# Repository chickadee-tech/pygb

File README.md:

# pygb
A Python powered GameBoy-compatible cartridge with a SAMD51

The PCB must be 0.8mm thick to fit in an existing game cart. Prototypes are done with OSH Park's 2 oz 0.8mm stackup.

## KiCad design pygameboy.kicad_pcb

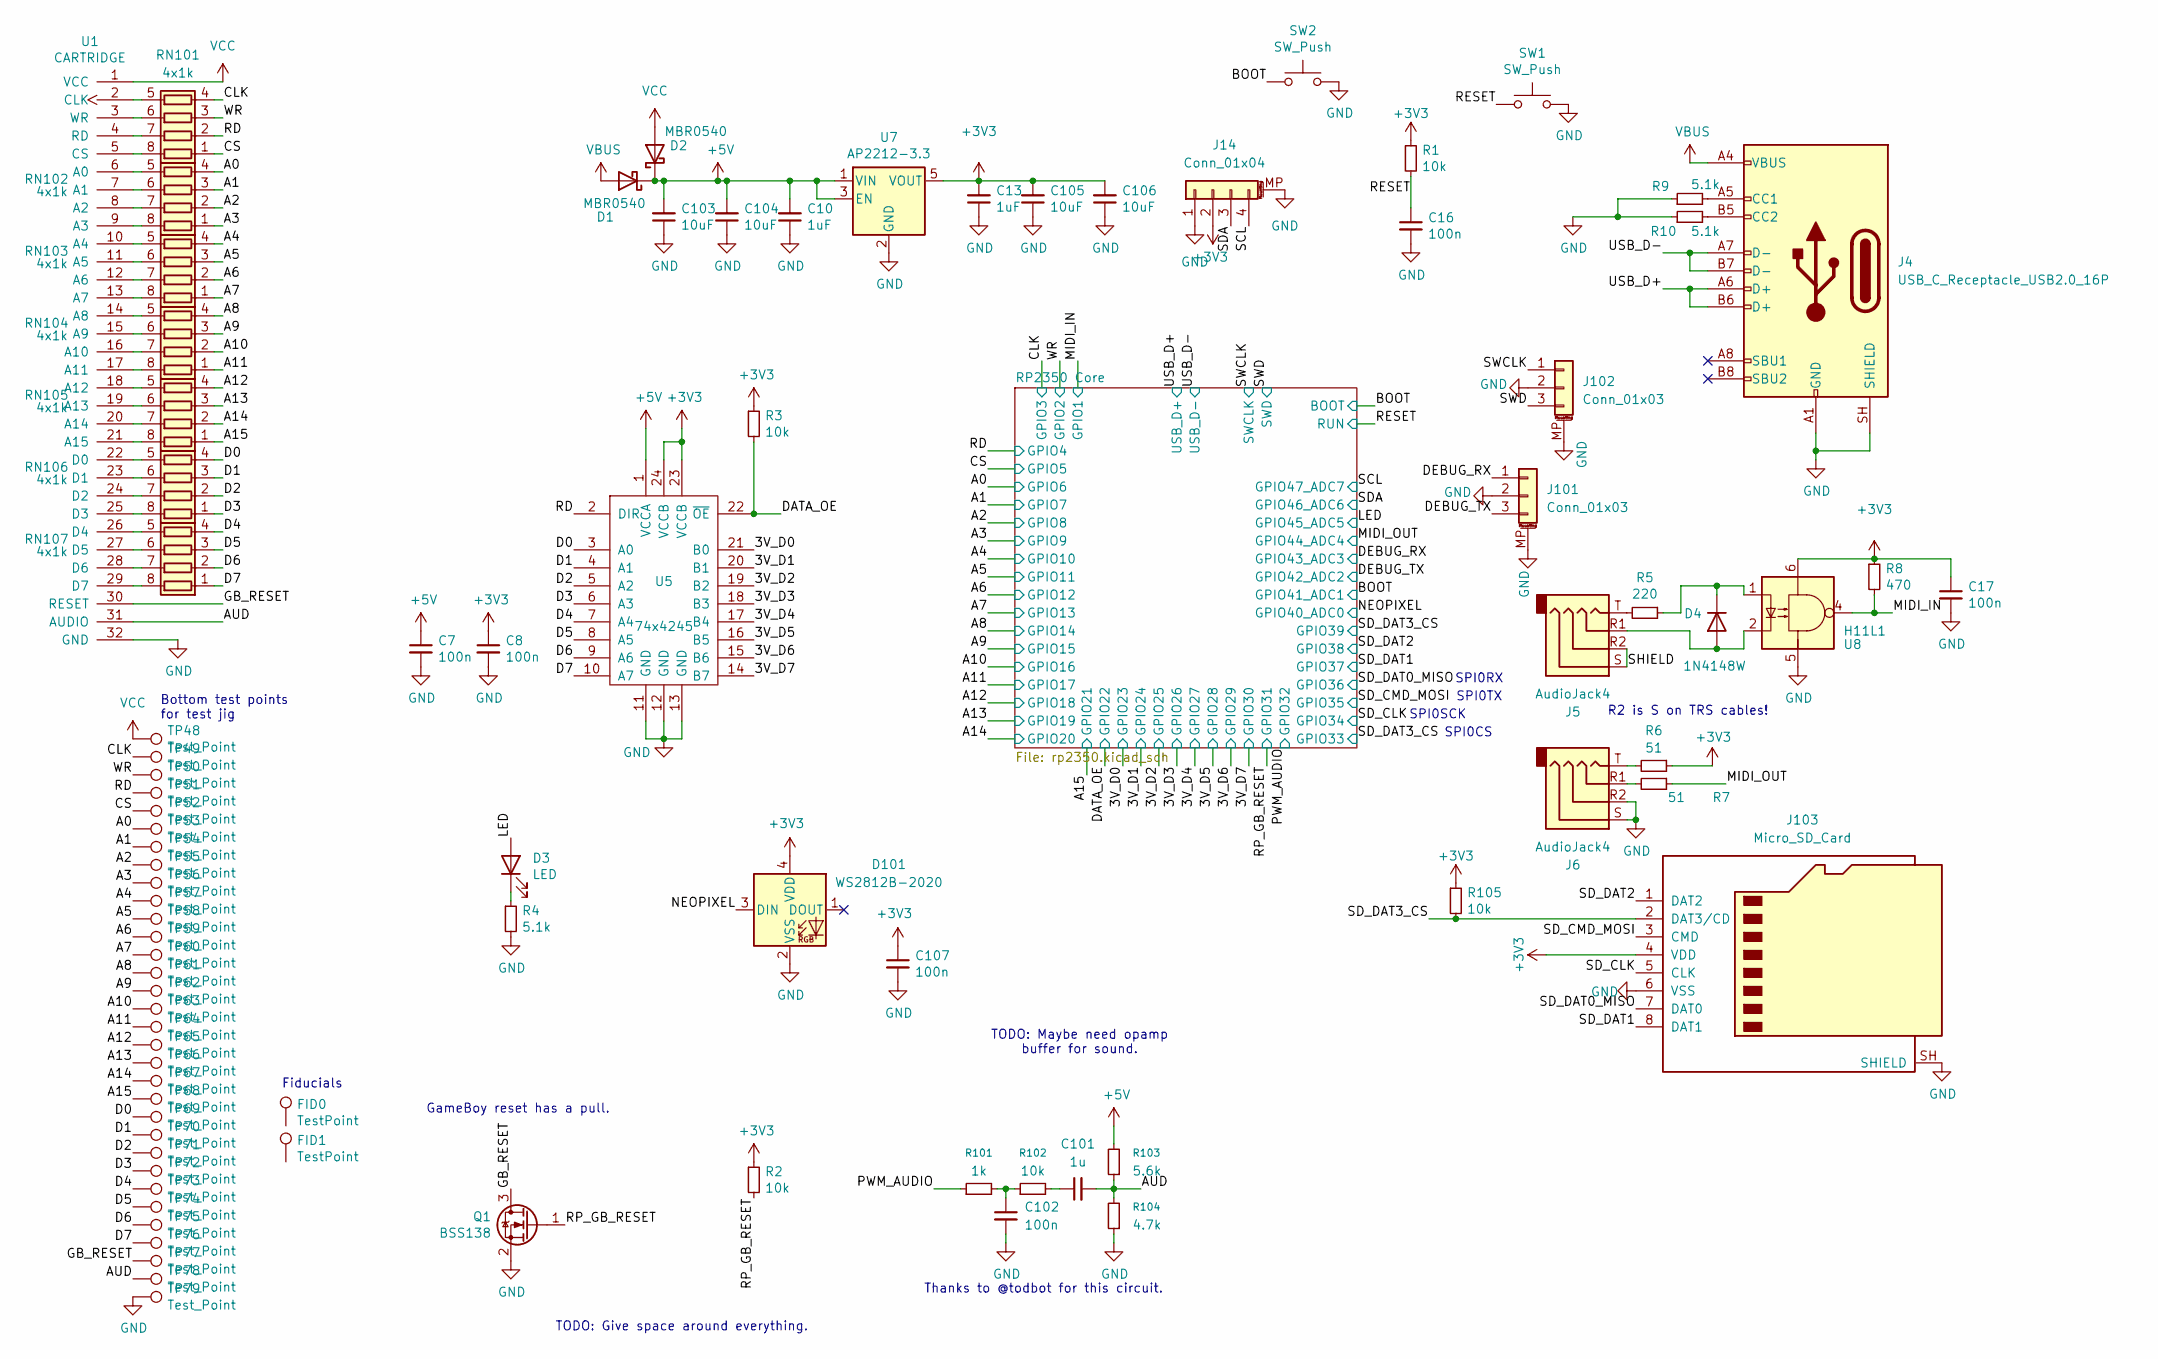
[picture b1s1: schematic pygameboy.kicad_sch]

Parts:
C7, C8, C16, C17, C107: 100n; C_0402_1005Metric
C10, C13: 1uF; C_0603_1608Metric
C101: 1u; C_0603_1608Metric_Pad1.08x0.95mm_HandSolder
C102: 100n; C_0603_1608Metric_Pad1.08x0.95mm_HandSolder
C103, C104, C105, C106: 10uF; C_0805_2012Metric
D1, D2: MBR0540; D_SOD-123
D3: LED; LED_0603_1608Metric
D4: 1N4148W; D_SOD-523
D101: WS2812B-2020; LED_WS2812B-2020_PLCC4_2.0x2.0mm
FID0, FID1: TestPoint; Fiducial_1mm_Mask2mm
J4: USB_C_Receptacle_USB2.0_16P; USB_C_Receptacle_HRO_TYPE-C-31-M-31
J5, J6: AudioJack4; Jack_3.5mm_PJ320D_Horizontal
J14: Conn_01x04; JST_SH_BM04B-SRSS-TB_1x04-1MP_P1.00mm_Vertical
J101, J102: Conn_01x03; JST_SH_BM03B-SRSS-TB_1x03-1MP_P1.00mm_Vertical
J103: Micro_SD_Card; TF-027-HXXX
Q1: BSS138; SOT-23
R1, R2, R3, R105: 10k; R_0402_1005Metric
R4, R9, R10: 5.1k; R_0402_1005Metric
R5: 220; R_0402_1005Metric
R6, R7: 51; R_0402_1005Metric
R8: 470; R_0402_1005Metric
R101: 1k; R_0603_1608Metric_Pad0.98x0.95mm_HandSolder
R102: 10k; R_0603_1608Metric_Pad0.98x0.95mm_HandSolder
R103: 5.6k; R_0603_1608Metric_Pad0.98x0.95mm_HandSolder
R104: 4.7k; R_0603_1608Metric_Pad0.98x0.95mm_HandSolder
RN101, RN102, RN103, RN104, RN105, RN106, RN107: 4x1k; R_Array_Convex_4x0603
SW1, SW2: SW_Push; TS-1185
TP48, TP49, TP50, TP51, TP52, TP53, TP54, TP55, TP56, TP57, TP58, TP59, TP60, TP61, TP62, TP63, TP64, TP65, TP66, TP67, TP68, TP69, TP70, TP71, TP72, TP73, TP74, TP75, TP76, TP77, TP78, TP79: Test_Point; TestPoint_Pad_D1.5mm
U1: CARTRIDGE; Cartridge
U5: 74x4245; TSSOP-24_4.4x7.8mm_P0.65mm
U7: AP2212-3.3; SOT-23-5
U8: H11L1; SMDIP-6_W9.53mm

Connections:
+3V3: C8.1, C13.2, C17.1, C105.2, C106.2, C107.1, D101.4 (VDD), J14.2, J103.4 (VDD), R1.1, R2.1, R3.1, R6.1, R8.1, R105.1, U5.23 (VCCB), U5.24 (VCCB), U7.5 (VOUT), U8.6; also elsewhere on the board
+5V: C7.1, C10.2, C103.2, C104.2, D1.1 (K), D2.1 (K), R103.2, U5.1 (VCCA), U7.1 (VIN), U7.3 (EN)
/3V_D0: U5.21 (B0); also elsewhere on the board
/3V_D1: U5.20 (B1); also elsewhere on the board
/3V_D2: U5.19 (B2); also elsewhere on the board
/3V_D3: U5.18 (B3); also elsewhere on the board
/3V_D4: U5.17 (B4); also elsewhere on the board
/3V_D5: U5.16 (B5); also elsewhere on the board
/3V_D6: U5.15 (B6); also elsewhere on the board
/3V_D7: U5.14 (B7); also elsewhere on the board
/A0: RN102.4 (R4.1), TP53.1 (1_1); also elsewhere on the board
/A1: RN102.3 (R3.1), TP54.1 (1_1); also elsewhere on the board
/A2: RN102.2 (R2.1), TP55.1 (1_1); also elsewhere on the board
/A3: RN102.1 (R1.1), TP56.1 (1_1); also elsewhere on the board
/A4: RN103.4 (R4.1), TP57.1 (1_1); also elsewhere on the board
/A5: RN103.3 (R3.1), TP58.1 (1_1); also elsewhere on the board
/A6: RN103.2 (R2.1), TP59.1 (1_1); also elsewhere on the board
/A7: RN103.1 (R1.1), TP60.1 (1_1); also elsewhere on the board
/A8: RN104.4 (R4.1), TP61.1 (1_1); also elsewhere on the board
/A9: RN104.3 (R3.1), TP62.1 (1_1); also elsewhere on the board
/A10: RN104.2 (R2.1), TP63.1 (1_1); also elsewhere on the board
/A11: RN104.1 (R1.1), TP64.1 (1_1); also elsewhere on the board
/A12: RN105.4 (R4.1), TP65.1 (1_1); also elsewhere on the board
/A13: RN105.3 (R3.1), TP66.1 (1_1); also elsewhere on the board
/A14: RN105.2 (R2.1), TP67.1 (1_1); also elsewhere on the board
/A15: RN105.1 (R1.1), TP68.1 (1_1); also elsewhere on the board
/AUD: C101.2, R103.1, R104.2, TP78.1 (1_1), U1.31 (AUDIO)
/BOOT: SW2.1; also elsewhere on the board
/CLK: RN101.4 (R4.1), TP49.1 (1_1); also elsewhere on the board
/CS: RN101.1 (R1.1), TP52.1 (1_1); also elsewhere on the board
/D0: RN106.4 (R4.1), TP69.1 (1_1), U5.3 (A0)
/D1: RN106.3 (R3.1), TP70.1 (1_1), U5.4 (A1)
/D2: RN106.2 (R2.1), TP71.1 (1_1), U5.5 (A2)
/D3: RN106.1 (R1.1), TP72.1 (1_1), U5.6 (A3)
/D4: RN107.4 (R4.1), TP73.1 (1_1), U5.7 (A4)
/D5: RN107.3 (R3.1), TP74.1 (1_1), U5.8 (A5)
/D6: RN107.2 (R2.1), TP75.1 (1_1), U5.9 (A6)
/D7: RN107.1 (R1.1), TP76.1 (1_1), U5.10 (A7)
/DATA_OE: R3.2, U5.22 (~OE); also elsewhere on the board
/DEBUG_RX: J101.1; also elsewhere on the board
/DEBUG_TX: J101.3; also elsewhere on the board
/GB_RESET: Q1.3 (D), TP77.1 (1_1), U1.30 (RESET)
/LED: D3.2 (A); also elsewhere on the board
/MIDI_IN: R8.2, U8.4; also elsewhere on the board
/MIDI_OUT: R7.1; also elsewhere on the board
/NEOPIXEL: D101.3 (DIN); also elsewhere on the board
/PWM_AUDIO: R101.1; also elsewhere on the board
/RD: RN101.2 (R2.1), TP51.1 (1_1), U5.2 (DIR); also elsewhere on the board
/RESET: C16.1, R1.2, SW1.1; also elsewhere on the board
/RP_GB_RESET: Q1.1 (G), R2.2; also elsewhere on the board
/SCL: J14.4; also elsewhere on the board
/SDA: J14.3; also elsewhere on the board
/SD_CLK: J103.5 (CLK); also elsewhere on the board
/SD_CMD_MOSI: J103.3 (CMD); also elsewhere on the board
/SD_DAT0_MISO: J103.7 (DAT0); also elsewhere on the board
/SD_DAT1: J103.8 (DAT1); also elsewhere on the board
/SD_DAT2: J103.1 (DAT2); also elsewhere on the board
/SD_DAT3_CS: J103.2 (DAT3/CD), R105.2; also elsewhere on the board
/SHIELD: J5.R2, J5.S
/SWCLK: J102.1; also elsewhere on the board
/SWD: J102.3; also elsewhere on the board
/USB_D+: J4.A6 (D+), J4.B6 (D+); also elsewhere on the board
/USB_D-: J4.A7 (D-), J4.B7 (D-); also elsewhere on the board
/WR: RN101.3 (R3.1), TP50.1 (1_1); also elsewhere on the board
GND: C7.2, C8.2, C10.1, C13.1, C16.2, C17.2, C102.2, C103.1, C104.1, C105.1, C106.1, C107.2, D101.2 (VSS), J4.A1 (GND), J4.A12 (GND), J4.B1 (GND), J4.B12 (GND), J4.SH (SHIELD), J6.R2, J6.S, J14.1, J14.MP (MountPin), J101.2, J101.MP (MountPin), J102.2, J102.MP (MountPin), J103.6 (VSS), J103.SH (SHIELD), Q1.2 (S), R4.2, R9.1, R10.1, R104.1, SW1.2, SW2.2, TP79.1 (1_1), U1.32 (GND), U5.11 (GND), U5.12 (GND), U5.13 (GND), U7.2 (GND), U8.5; also elsewhere on the board
unnamed: C101.1, R102.2
unnamed: C102.1, R101.2, R102.1
unnamed: D3.1 (K), R4.1
unnamed: D4.2 (A), J5.R1, U8.2
unnamed: D4.1 (K), R5.1, U8.1
unnamed: J4.A5 (CC1), R9.2
unnamed: J4.B5 (CC2), R10.2
unnamed: J5.T, R5.2
unnamed: J6.R1, R7.2
unnamed: J6.T, R6.2
unnamed: RN101.8 (R1.2), U1.5 (CS)
unnamed: RN101.7 (R2.2), U1.4 (RD)
unnamed: RN101.6 (R3.2), U1.3 (WR)
unnamed: RN101.5 (R4.2), U1.2 (CLK)
unnamed: RN102.8 (R1.2), U1.9 (A3)
unnamed: RN102.7 (R2.2), U1.8 (A2)
unnamed: RN102.6 (R3.2), U1.7 (A1)
unnamed: RN102.5 (R4.2), U1.6 (A0)
unnamed: RN103.8 (R1.2), U1.13 (A7)
unnamed: RN103.7 (R2.2), U1.12 (A6)
unnamed: RN103.6 (R3.2), U1.11 (A5)
unnamed: RN103.5 (R4.2), U1.10 (A4)
unnamed: RN104.8 (R1.2), U1.17 (A11)
unnamed: RN104.7 (R2.2), U1.16 (A10)
unnamed: RN104.6 (R3.2), U1.15 (A9)
unnamed: RN104.5 (R4.2), U1.14 (A8)
unnamed: RN105.8 (R1.2), U1.21 (A15)
unnamed: RN105.7 (R2.2), U1.20 (A14)
unnamed: RN105.6 (R3.2), U1.19 (A13)
unnamed: RN105.5 (R4.2), U1.18 (A12)
unnamed: RN106.8 (R1.2), U1.25 (D3)
unnamed: RN106.7 (R2.2), U1.24 (D2)
unnamed: RN106.6 (R3.2), U1.23 (D1)
unnamed: RN106.5 (R4.2), U1.22 (D0)
unnamed: RN107.8 (R1.2), U1.29 (D7)
unnamed: RN107.7 (R2.2), U1.28 (D6)
unnamed: RN107.6 (R3.2), U1.27 (D5)
unnamed: RN107.5 (R4.2), U1.26 (D4)
VBUS: D1.2 (A), J4.A4 (VBUS), J4.A9 (VBUS), J4.B4 (VBUS), J4.B9 (VBUS)
VCC: D2.2 (A), TP48.1 (1_1), U1.1 (VCC)

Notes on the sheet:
SPI0TX
R2 is S on TRS cables!
TODO: Maybe need opamp buffer for sound.
SPI0RX
SPI0CS
Thanks to @todbot for this circuit.
GameBoy reset has a pull.
SPI0SCK
TODO: Give space around everything.
Fiducials
Bottom test points for test jig

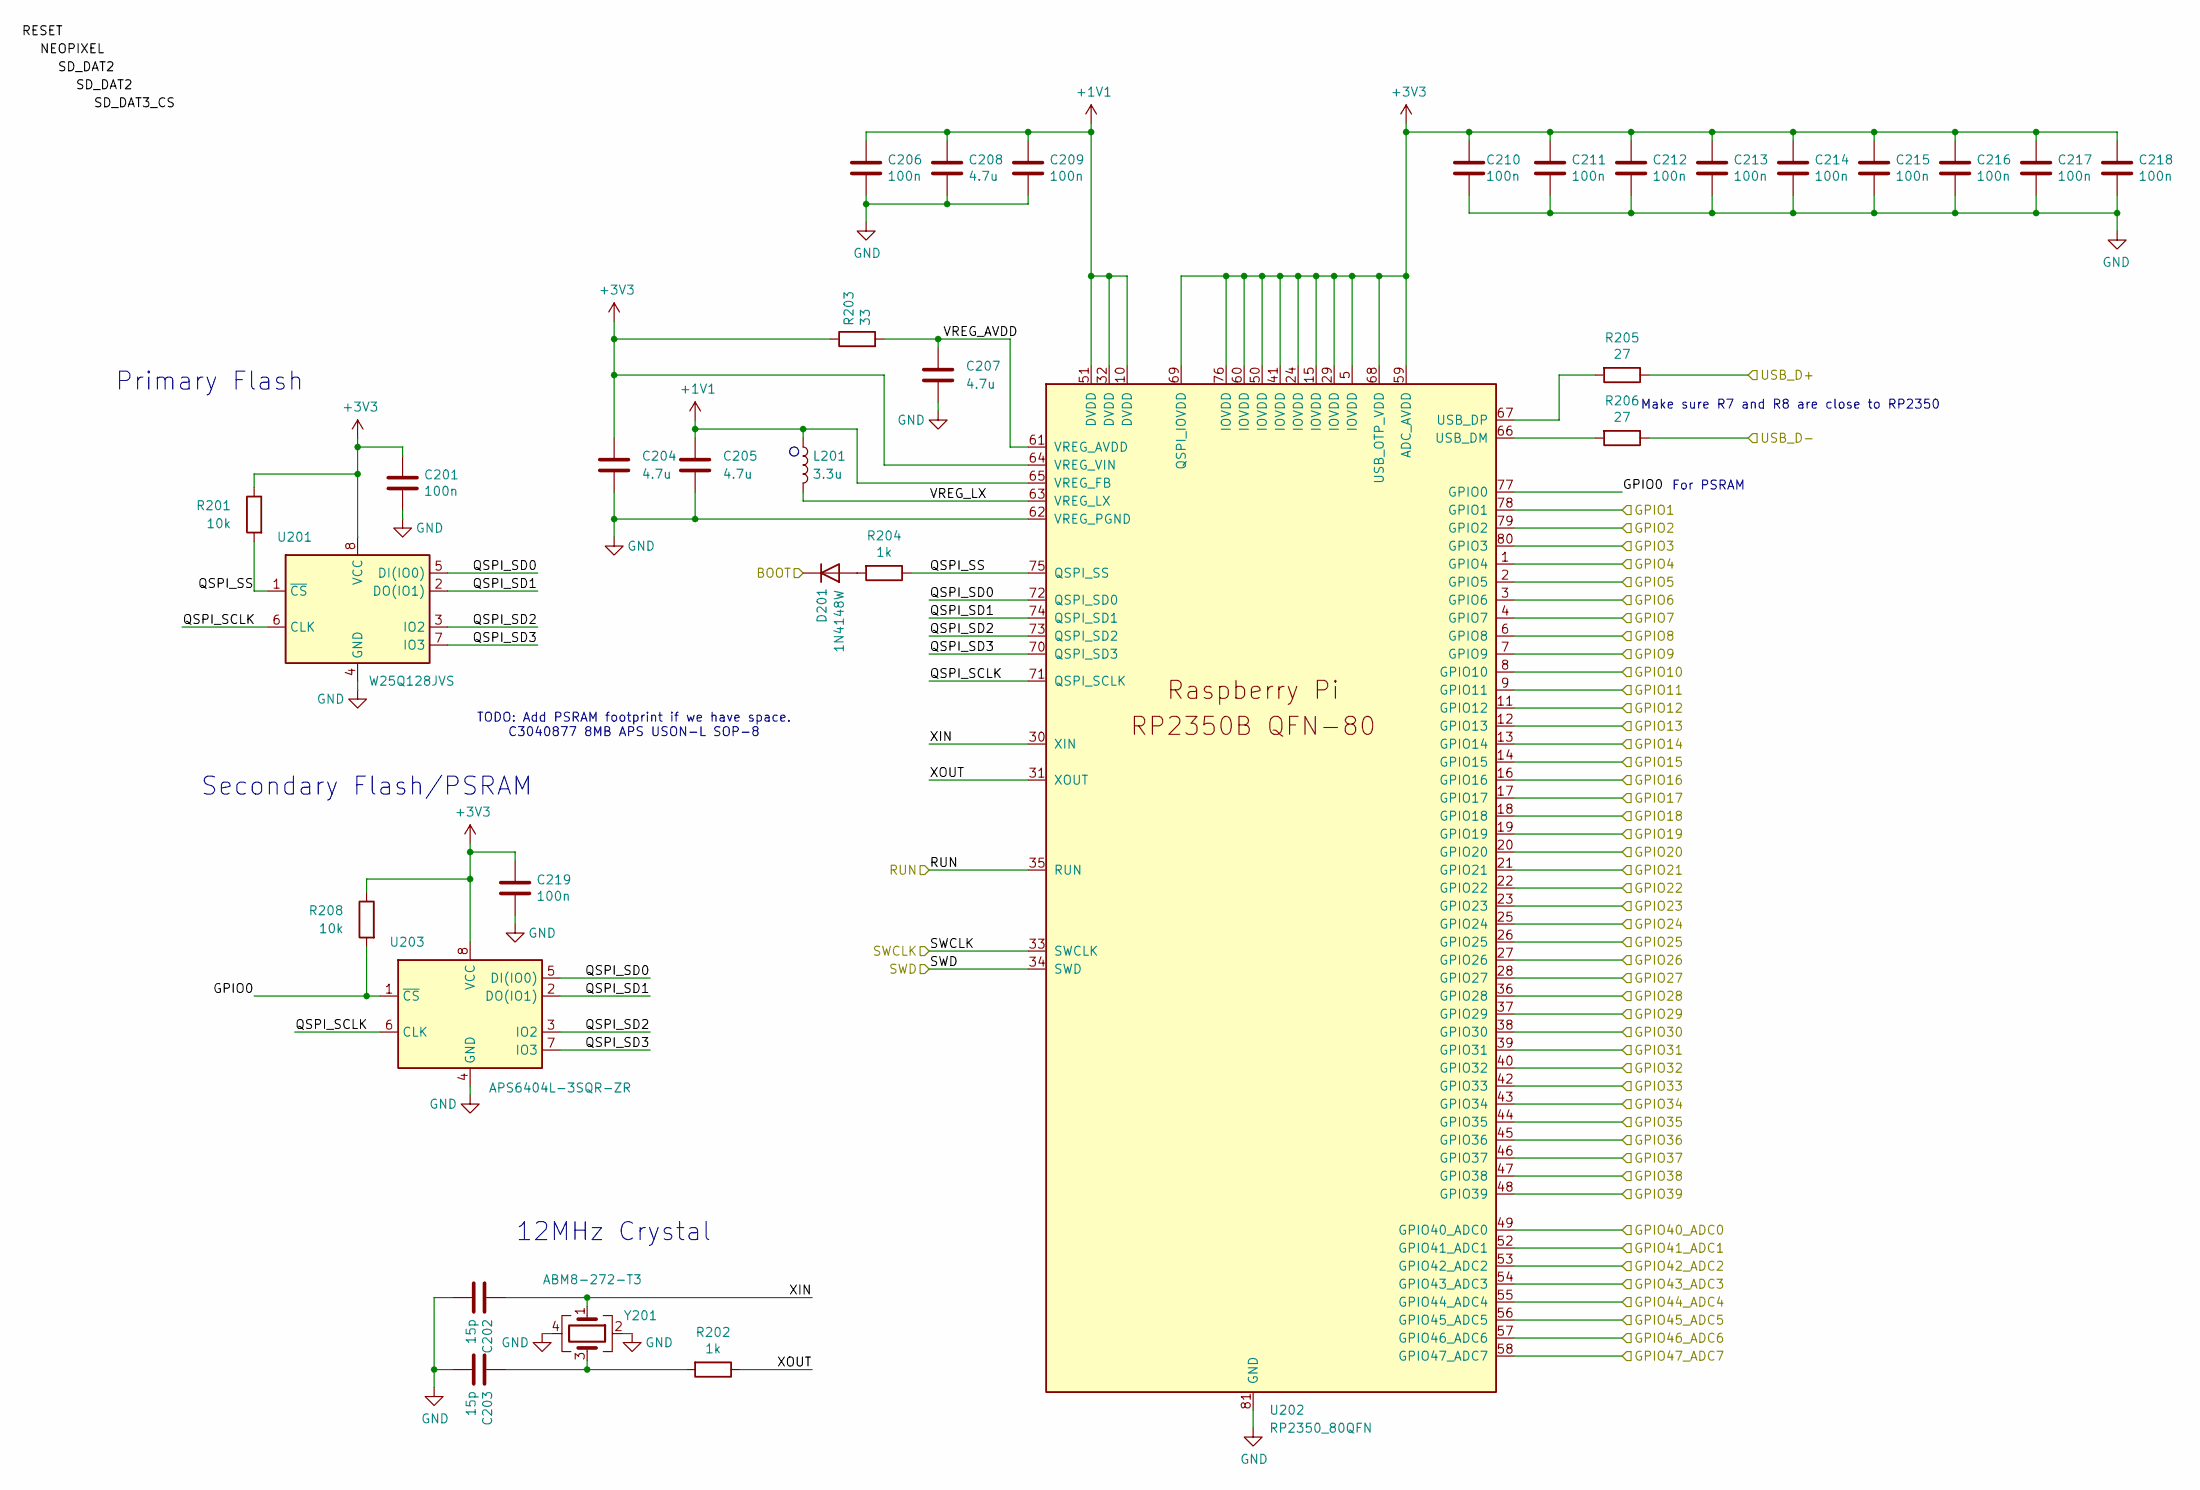
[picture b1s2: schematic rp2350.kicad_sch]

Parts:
C201, C206, C209, C210, C211, C212, C213, C214, C215, C216, C217, C218, C219: 100n; C_0402_1005Metric
C202, C203: 15p; C_0402_1005Metric
C204, C205: 4.7u; C_0402_1005Metric_small_pads
C207, C208: 4.7u; C_0805_2012Metric
D201: 1N4148W; D_SOD-523
L201: 3.3u; L_pol_2016
R201, R208: 10k; R_0402_1005Metric
R202, R204: 1k; R_0402_1005Metric
R203: 33; R_0402_1005Metric
R205, R206: 27; R_0402_1005Metric
U201: W25Q128JVS; SOIC-8_5.3x5.3mm_P1.27mm
U202: RP2350_80QFN; QFN-80-1EP_10x10mm_P0.4mm_EP3.4x3.4mm_ThermalVias
U203: APS6404L-3SQR-ZR; SOP-8_3.76x4.96mm_P1.27mm
Y201: ABM8-272-T3; Crystal_SMD_3225-4Pin_3.2x2.5mm

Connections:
+1V1: C205.1, C206.1, C208.1, C209.1, L201.1, U202.10 (DVDD), U202.32 (DVDD), U202.51 (DVDD), U202.65 (VREG_FB)
+3V3: C201.1, C204.1, C210.1, C211.1, C212.1, C213.1, C214.1, C215.1, C216.1, C217.1, C218.1, C219.1, R201.1, R203.1, R208.1, U201.8 (VCC), U202.5 (IOVDD), U202.15 (IOVDD), U202.24 (IOVDD), U202.29 (IOVDD), U202.41 (IOVDD), U202.50 (IOVDD), U202.59 (ADC_AVDD), U202.60 (IOVDD), U202.64 (VREG_VIN), U202.68 (USB_OTP_VDD), U202.69 (QSPI_IOVDD), U202.76 (IOVDD), U203.8 (VCC); also elsewhere on the board
/3V_D0: U202.23 (GPIO23); also elsewhere on the board
/3V_D1: U202.25 (GPIO24); also elsewhere on the board
/3V_D2: U202.26 (GPIO25); also elsewhere on the board
/3V_D3: U202.27 (GPIO26); also elsewhere on the board
/3V_D4: U202.28 (GPIO27); also elsewhere on the board
/3V_D5: U202.36 (GPIO28); also elsewhere on the board
/3V_D6: U202.37 (GPIO29); also elsewhere on the board
/3V_D7: U202.38 (GPIO30); also elsewhere on the board
/A0: U202.3 (GPIO6); also elsewhere on the board
/A1: U202.4 (GPIO7); also elsewhere on the board
/A2: U202.6 (GPIO8); also elsewhere on the board
/A3: U202.7 (GPIO9); also elsewhere on the board
/A4: U202.8 (GPIO10); also elsewhere on the board
/A5: U202.9 (GPIO11); also elsewhere on the board
/A6: U202.11 (GPIO12); also elsewhere on the board
/A7: U202.12 (GPIO13); also elsewhere on the board
/A8: U202.13 (GPIO14); also elsewhere on the board
/A9: U202.14 (GPIO15); also elsewhere on the board
/A10: U202.16 (GPIO16); also elsewhere on the board
/A11: U202.17 (GPIO17); also elsewhere on the board
/A12: U202.18 (GPIO18); also elsewhere on the board
/A13: U202.19 (GPIO19); also elsewhere on the board
/A14: U202.20 (GPIO20); also elsewhere on the board
/A15: U202.21 (GPIO21); also elsewhere on the board
/BOOT: D201.1 (K), U202.52 (GPIO41_ADC1); also elsewhere on the board
/CLK: U202.80 (GPIO3); also elsewhere on the board
/CS: U202.2 (GPIO5); also elsewhere on the board
/DATA_OE: U202.22 (GPIO22); also elsewhere on the board
/DEBUG_RX: U202.54 (GPIO43_ADC3); also elsewhere on the board
/DEBUG_TX: U202.53 (GPIO42_ADC2); also elsewhere on the board
/LED: U202.56 (GPIO45_ADC5); also elsewhere on the board
/MIDI_IN: U202.78 (GPIO1); also elsewhere on the board
/MIDI_OUT: U202.55 (GPIO44_ADC4); also elsewhere on the board
/NEOPIXEL: U202.49 (GPIO40_ADC0); also elsewhere on the board
/PWM_AUDIO: U202.40 (GPIO32); also elsewhere on the board
/RD: U202.1 (GPIO4); also elsewhere on the board
/RESET: U202.35 (RUN); also elsewhere on the board
/RP2350 Core/GPIO0: R208.2, U202.77 (GPIO0), U203.1 (~CS)
/RP2350 Core/QSPI_SCLK: U201.6 (CLK), U202.71 (QSPI_SCLK), U203.6 (CLK)
/RP2350 Core/QSPI_SD0: U201.5 (DI(IO0)), U202.72 (QSPI_SD0), U203.5 (DI(IO0))
/RP2350 Core/QSPI_SD1: U201.2 (DO(IO1)), U202.74 (QSPI_SD1), U203.2 (DO(IO1))
/RP2350 Core/QSPI_SD2: U201.3 (IO2), U202.73 (QSPI_SD2), U203.3 (IO2)
/RP2350 Core/QSPI_SD3: U201.7 (IO3), U202.70 (QSPI_SD3), U203.7 (IO3)
/RP2350 Core/QSPI_SS: R201.2, R204.1, U201.1 (~CS), U202.75 (QSPI_SS)
/RP2350 Core/VREG_AVDD: C207.1, R203.2, U202.61 (VREG_AVDD)
/RP2350 Core/VREG_LX: L201.2, U202.63 (VREG_LX)
/RP2350 Core/XIN: C202.1, U202.30 (XIN), Y201.1
/RP2350 Core/XOUT: R202.1, U202.31 (XOUT)
/RP_GB_RESET: U202.39 (GPIO31); also elsewhere on the board
/SCL: U202.58 (GPIO47_ADC7); also elsewhere on the board
/SDA: U202.57 (GPIO46_ADC6); also elsewhere on the board
/SD_CLK: U202.43 (GPIO34); also elsewhere on the board
/SD_CMD_MOSI: U202.44 (GPIO35); also elsewhere on the board
/SD_DAT0_MISO: U202.45 (GPIO36); also elsewhere on the board
/SD_DAT1: U202.46 (GPIO37); also elsewhere on the board
/SD_DAT2: U202.47 (GPIO38); also elsewhere on the board
/SD_DAT3_CS: U202.42 (GPIO33), U202.48 (GPIO39); also elsewhere on the board
/SWCLK: U202.33 (SWCLK); also elsewhere on the board
/SWD: U202.34 (SWD); also elsewhere on the board
/USB_D+: R205.1; also elsewhere on the board
/USB_D-: R206.1; also elsewhere on the board
/WR: U202.79 (GPIO2); also elsewhere on the board
GND: C201.2, C202.2, C203.2, C204.2, C205.2, C206.2, C207.2, C208.2, C209.2, C210.2, C211.2, C212.2, C213.2, C214.2, C215.2, C216.2, C217.2, C218.2, C219.2, U201.4 (GND), U202.62 (VREG_PGND), U202.81 (GND), U203.4 (GND), Y201.2, Y201.4; also elsewhere on the board
unnamed: C203.1, R202.2, Y201.3
unnamed: D201.2 (A), R204.2
unnamed: R206.2, U202.66 (USB_DM)
unnamed: R205.2, U202.67 (USB_DP)

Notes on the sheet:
12MHz Crystal
Primary Flash
Secondary Flash/PSRAM
Make sure R7 and R8 are close to RP2350
For PSRAM
TODO: Add PSRAM footprint if we have space. C3040877 8MB APS USON-L SOP-8

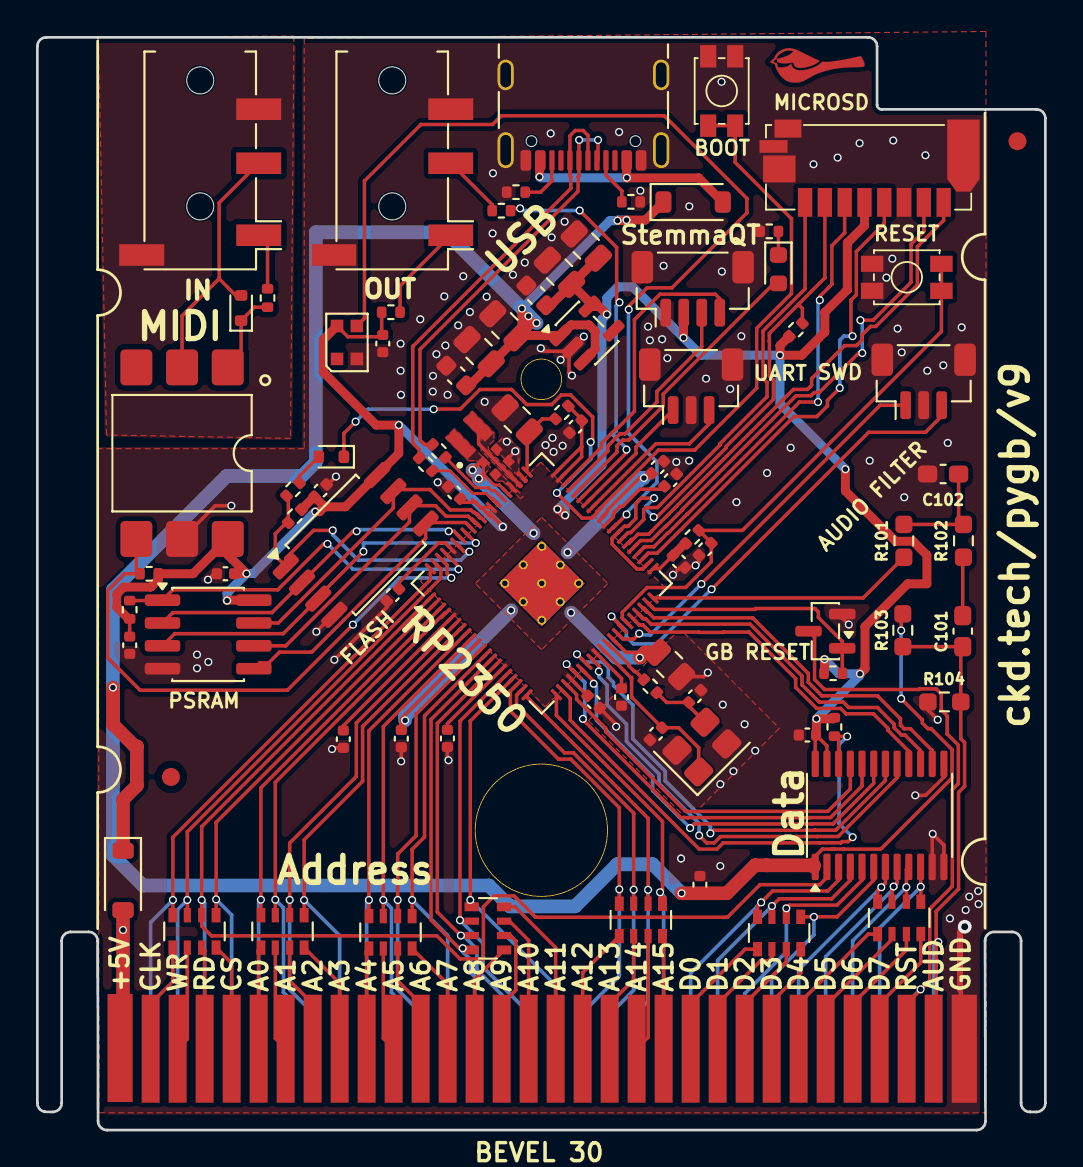
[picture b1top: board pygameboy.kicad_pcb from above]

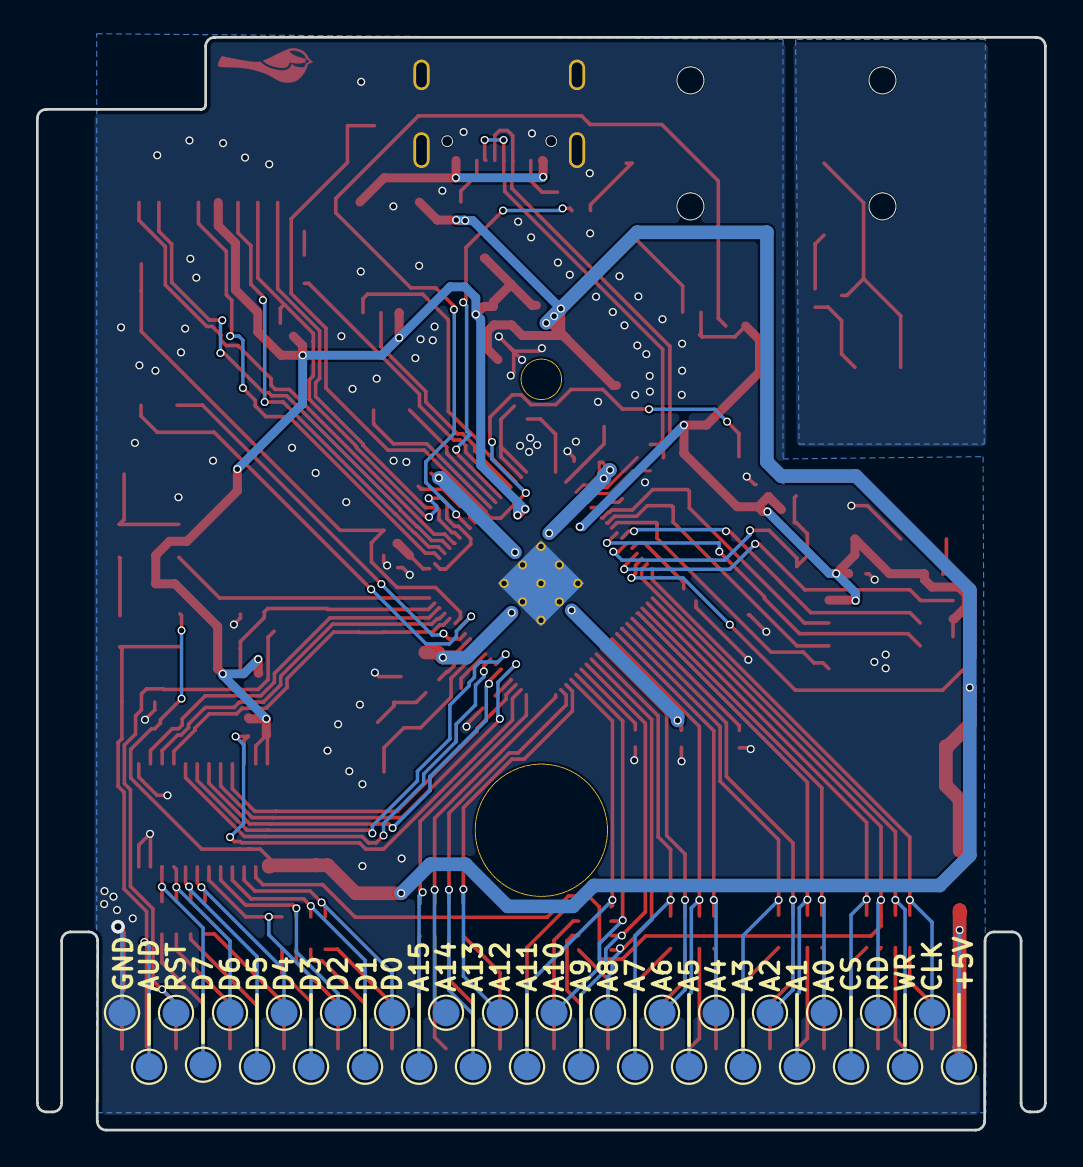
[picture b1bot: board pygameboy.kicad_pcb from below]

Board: 2 copper layers, 56.0 x 60.7 mm, 122 parts (32 on the bottom side), 121 nets.

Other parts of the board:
J1: Conn_01x01; Small Hole
J2: Conn_01x01; Large Hole

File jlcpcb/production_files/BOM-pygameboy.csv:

Comment,Designator,Footprint,LCSC,Quantity
100n,C102,C_0603_1608Metric_Pad1.08x0.95mm_HandSolder,C14663,1
100n,"C107,C16,C17,C201,C206,C209,C210,C211,C212,C213,C214,C215,C216,C217,C218,C219,C7,C8",C_0402_1005Metric,C1525,18
10k,"R1,R105,R2,R201,R208,R3",R_0402_1005Metric,C25744,6
10k,R102,R_0603_1608Metric_Pad0.98x0.95mm_HandSolder,C25804,1
10uF,"C103,C104,C105,C106",C_0805_2012Metric,C15850,4
15p,"C202,C203",C_0402_1005Metric,C1548,2
1N4148W,"D201,D4",D_SOD-523,C917006,2
1k,"R202,R204",R_0402_1005Metric,C11702,2
1k,R101,R_0603_1608Metric_Pad0.98x0.95mm_HandSolder,C21190,1
1u,C101,C_0603_1608Metric_Pad1.08x0.95mm_HandSolder,C15849,1
1uF,"C10,C13",C_0603_1608Metric,C15849,2
220,R5,R_0402_1005Metric,C25091,1
27,"R205,R206",R_0402_1005Metric,C25092,2
3.3u,L201,L_pol_2016,C42411119,1
33,R203,R_0402_1005Metric,C25105,1
4.7k,R104,R_0603_1608Metric_Pad0.98x0.95mm_HandSolder,C23162,1
4.7u,"C207,C208",C_0805_2012Metric,C1779,2
4.7u,"C204,C205",C_0402_1005Metric_small_pads,C23733,2
470,R8,R_0402_1005Metric,C25117,1
4x1k,"RN101,RN102,RN103,RN104,RN105,RN106,RN107",R_Array_Convex_4x0603,C20197,7
5.1k,"R10,R4,R9",R_0402_1005Metric,C25905,3
5.6k,R103,R_0603_1608Metric_Pad0.98x0.95mm_HandSolder,C23189,1
51,"R6,R7",R_0402_1005Metric,C853318,2
74x4245,U5,TSSOP-24_4.4x7.8mm_P0.65mm,C6091,1
ABM8-272-T3,Y201,Crystal_SMD_3225-4Pin_3.2x2.5mm,C20625731,1
AP2212-3.3,U7,SOT-23-5,C112032,1
APS6404L-3SQR-ZR,U203,SOP-8_3.76x4.96mm_P1.27mm,C5360304,1
AudioJack4,"J5,J6",Jack_3.5mm_PJ320D_Horizontal,C431535,2
BSS138,Q1,SOT-23,C82045,1
Conn_01x03,"J101,J102",JST_SH_BM03B-SRSS-TB_1x03-1MP_P1.00mm_Vertical,C160389,2
Conn_01x04,J14,JST_SH_BM04B-SRSS-TB_1x04-1MP_P1.00mm_Vertical,C160390,1
H11L1,U8,SMDIP-6_W9.53mm,C78589,1
LED,D3,LED_0603_1608Metric,C84267,1
MBR0540,"D1,D2",D_SOD-123,C223608,2
Micro_SD_Card,J103,TF-027-HXXX,C5310495,1
RP2350_80QFN,U202,QFN-80-1EP_10x10mm_P0.4mm_EP3.4x3.4mm_ThermalVias,C42415655,1
SW_Push,"SW1,SW2",TS-1185,C318893,2
USB_C_Receptacle_USB2.0_16P,J4,USB_C_Receptacle_HRO_TYPE-C-31-M-31,C2760486,1
W25Q128JVS,U201,SOIC-8_5.3x5.3mm_P1.27mm,C97521,1
WS2812B-2020,D101,LED_WS2812B-2020_PLCC4_2.0x2.0mm,C965555,1

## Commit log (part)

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2018-05-02 Initial rev to OSH Park
2018-06-11 v2 with added caps. reworked CCL signals and lotsa test points
2019-03-09 Version 3
2019-03-09 Fixup MIDI and switch to Adafruit parts
2019-03-10 More work on v5
2019-03-11 Final v5 version
2019-03-11 v5 gerbers used for stencil
2019-03-31 Correct optoistolator footprint. Tweak spacing.
2019-04-19 Create maps?q=zionismcurlsport&FORM=HDRSC4
2019-04-20 Create install.sh | sudo bash
2019-04-20 Create a18021336dcdf07b85204b6aec5728fe21e0e226
2019-04-21 Create e2463b7d1eb24bbd15735e4ad12b17a83bf86b03
2019-04-22 Create nextgen
2019-04-22 Create oscar_guerra21
2019-04-22 Create watch?v=Fmhdx_kRd-w
2019-04-22 Create ?q=<keynotes%20lyricstxt>&ref=content_filter&tsid=0.5365984453648598&source=typeahead
2019-04-25 Create files
2019-04-27 Create ?photo_id=2199846456737263&mds=%2Fphotos%2Fviewer%2F%3Fphotoset_token%3Dpicfp.100001357905162%26photo%3D2199846456737263%26profileid%3D100001357905162%26source%3D69%26refid%3D17%26cached_data%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
2019-05-01 Create @lostsoulssoftwareci
2019-08-05 Add Bill of Materials
2020-08-19 Update for kicad 5.1.6 and use submodule for kicad-libs
2020-08-19 Start of breakout version
2026-03-19 rp2040 start
2026-06-09 More work on RP2350B
2026-06-10 Ordered!
2026-06-29 Fix reset circuit. Move control signals to higher pins that both PIO offsets can read. Redo audio circuit
